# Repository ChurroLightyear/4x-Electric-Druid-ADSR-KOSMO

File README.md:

# 4x-Electric-Druid-ADSR-KOSMO (UN TESTED)
A kind of crude envelope generator based around the ENVGEN 8C chip from electric druid and LMNC's circuit for the mini ADSR

I originally designed this on stripboard which It's worked great since but after moving my modules around and debugging over 50+ wires for which one may have shorted I decided to make a PCB layout. The old stripboard layout works fine but It's ALOT of wired connections and 2 boards.
This is a PCB layout for a 4 envelope generators based around LMNC's ADSR and the electric druid chip ENV GEN 8C.
This has the a level knob added and it's 6 knobs ADSR time and level with a mode switch (ADSR, Gated loop and loop) and 16 jacks (a gate input, 2 output and a negative output for each envelope)
Theres a panel layout with the holes for everything except the LED's which I added after. I'm still using my old painted aluminum panel for this but The space for optional LEDs are on the Main PCB.
There's also holes on the panel that fit the Tayda stripboard mounting holes.
The LEDs are connected directly to the output so there may be some voltage drop but I've not noticed anything on the stripboard version
This module is untested the stripboard layout works

The files for the PCBs are all layed out in Kicad

UPDATE circuit has been verified and tested but there is a single missing trace for envelope 3
Between R27 and R49 be sure to a trace or jumper between those Reuploading the fixed board

The files on github have been updated with the missing trace, Everything should work as expected.
Added a BOM for both boards***

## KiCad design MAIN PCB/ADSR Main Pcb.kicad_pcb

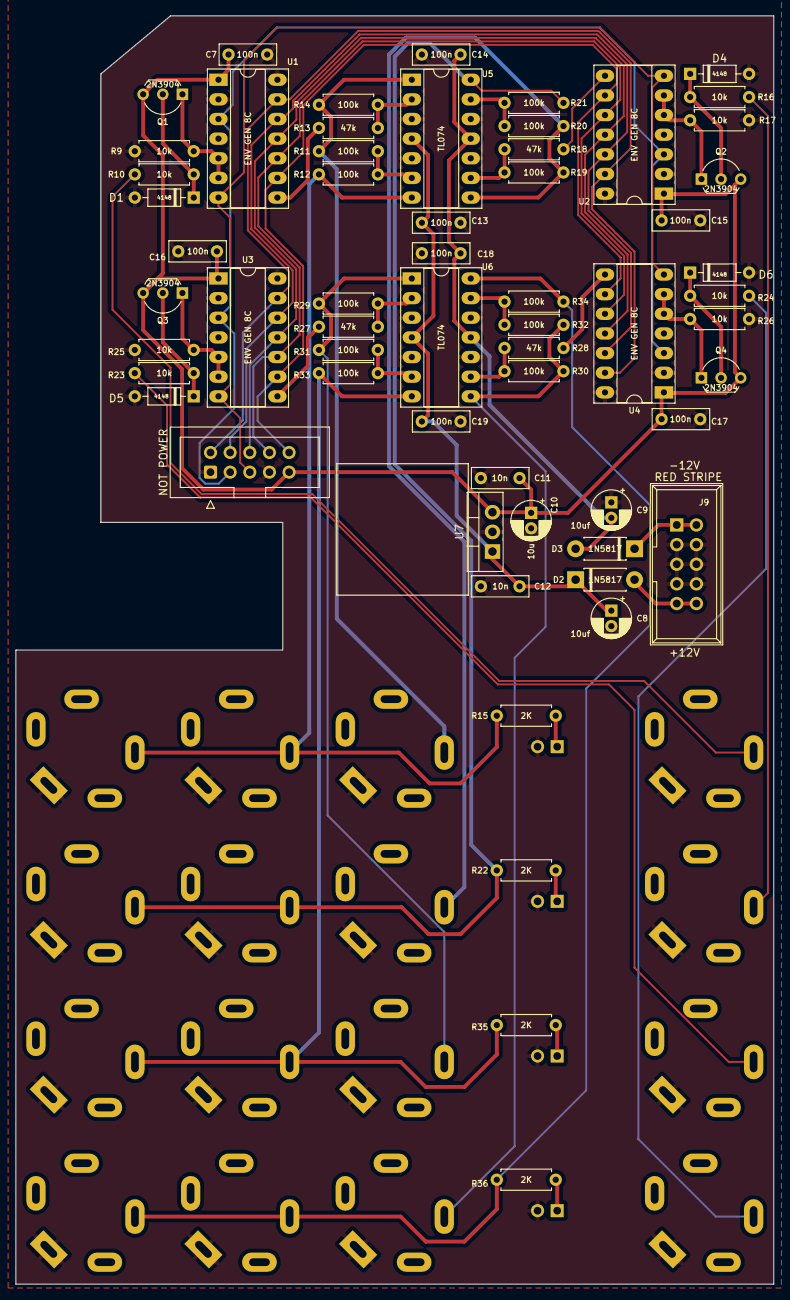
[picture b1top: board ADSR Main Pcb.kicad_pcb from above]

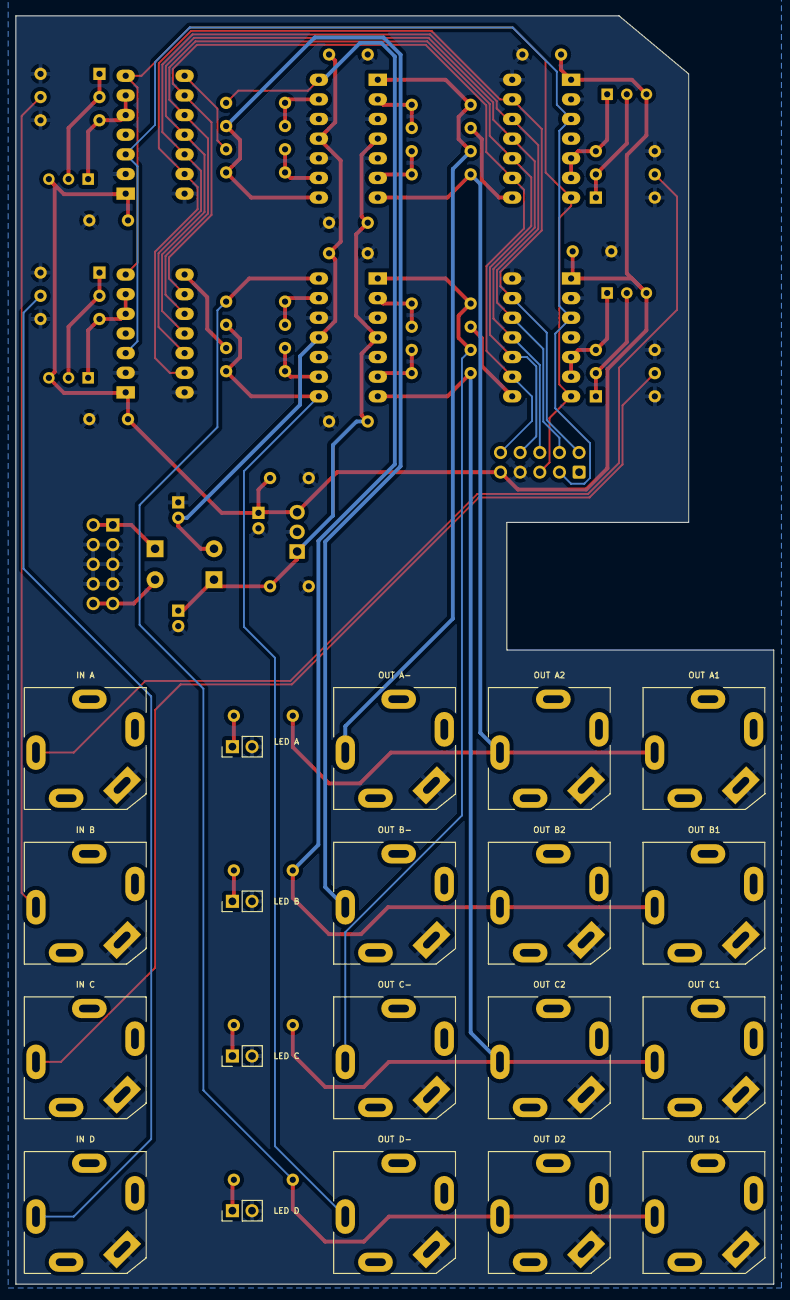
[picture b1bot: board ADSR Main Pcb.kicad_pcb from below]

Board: 2 copper layers, 98.0 x 164.0 mm, 80 parts (20 on the bottom side), 49 nets.

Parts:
C7, C13, C14, C15, C16, C17, C18, C19: 100n; C_Rect_L7.2mm_W2.5mm_P5.00mm_FKS2_FKP2_MKS2_MKP2
C8, C9: 10uf; CP_Radial_D5.0mm_P2.00mm
C10: 10u; CP_Radial_D5.0mm_P2.00mm
C11, C12: 10n; C_Rect_L7.2mm_W2.5mm_P5.00mm_FKS2_FKP2_MKS2_MKP2
D1, D4, D5, D6: 1N4148; D_DO-35_SOD27_P7.62mm_Horizontal
D2, D3: 1N5817; D_DO-41_SOD81_P7.62mm_Horizontal
IN A: Jack_6.35mm_PJ_629HAN_slots
IN B: Jack_6.35mm_PJ_629HAN_slots
IN C: Jack_6.35mm_PJ_629HAN_slots
IN D: Jack_6.35mm_PJ_629HAN_slots
J9: POWER; Power_Header
LED A: LED A; PinHeader_1x02_P2.54mm_Vertical
LED B: LED B; PinHeader_1x02_P2.54mm_Vertical
LED C: LED C; PinHeader_1x02_P2.54mm_Vertical
LED D: LED D; PinHeader_1x02_P2.54mm_Vertical
NOT POWER: IDC-Header_2x05_P2.54mm_Vertical
OUT A1, OUT A2: Jack_6.35mm_PJ_629HAN_slots
OUT A-: Jack_6.35mm_PJ_629HAN_slots
OUT B1, OUT B2: Jack_6.35mm_PJ_629HAN_slots
OUT B-: Jack_6.35mm_PJ_629HAN_slots
OUT C1, OUT C2: Jack_6.35mm_PJ_629HAN_slots
OUT C-: Jack_6.35mm_PJ_629HAN_slots
OUT D1, OUT D2: Jack_6.35mm_PJ_629HAN_slots
OUT D-: Jack_6.35mm_PJ_629HAN_slots
Q1, Q2, Q3, Q4: 2N3904; TO-92_Inline_Wide
R9, R10, R16, R17, R23, R24, R25, R26: 10k; R_Axial_DIN0207_L6.3mm_D2.5mm_P7.62mm_Horizontal
R11, R12, R14, R19, R20, R21, R29, R30, R31, R32, R33, R34: 100k; R_Axial_DIN0207_L6.3mm_D2.5mm_P7.62mm_Horizontal
R13, R18, R27, R28: 47k; R_Axial_DIN0207_L6.3mm_D2.5mm_P7.62mm_Horizontal
R15, R22, R35, R36: 2K; R_Axial_DIN0207_L6.3mm_D2.5mm_P7.62mm_Horizontal
U1, U2, U3, U4: ENV GEN 8C; DIP-14_W7.62mm_Socket_LongPads
U5, U6: TL074; DIP-14_W7.62mm_Socket_LongPads
U7: LM7809; TO-220-3_Vertical

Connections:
+5V: C7.2, C10.1, C11.1, C15.2, C16.2, C17.2, NOT POWER.9, Q1.3 (C), Q2.3 (C), Q3.3 (C), Q4.3 (C), U1.1 (5v), U2.1 (5v), U3.1 (5v), U4.1 (5v), U7.3 (VO)
+12V: C8.1, C12.2, C13.1, C19.1, D2.1 (K), U5.4 (V+), U6.4 (V+), U7.1 (VI)
-12V: C9.2, C14.2, C18.2, D3.2 (A), U5.11 (V-), U6.11 (V-)
ATK: NOT POWER.2, U1.13 (ATK), U2.13 (ATK), U3.13 (ATK), U4.13 (ATK)
DEC: NOT POWER.6, U1.11 (DEC), U2.11 (DEC), U3.11 (DEC), U4.11 (DEC)
ENV A: R13.1, U1.8 (OUT)
ENV B: R18.1, U2.8 (OUT)
ENV C: R27.1, U3.8 (OUT)
ENV D: R28.1, U4.8 (OUT)
GATE A: Q1.1 (E), R9.1, U1.5 (GATE), U1.6 (TRIG)
GATE B: Q2.1 (E), R17.1, U2.5 (GATE), U2.6 (TRIG)
GATE C: Q3.1 (E), R25.1, U3.5 (GATE), U3.6 (TRIG)
GATE D: Q4.1 (E), R26.1, U4.5 (GATE), U4.6 (TRIG)
GND: C7.1, C8.2, C9.1, C10.2, C11.2, C12.1, C13.2, C14.1, C15.1, C16.1, C17.1, C18.1, C19.2, D1.2 (A), D4.2 (A), D5.2 (A), D6.2 (A), IN A.S, IN B.S, IN C.S, IN D.S, J9.3 (GND), J9.4 (GND), J9.5 (GND), J9.6 (GND), J9.7 (GND), J9.8 (GND), LED A.2, LED B.2, LED C.2, LED D.2, NOT POWER.1, NOT POWER.7, OUT A1.S, OUT A2.S, OUT A-.S, OUT B1.S, OUT B2.S, OUT B-.S, OUT C1.S, OUT C2.S, OUT C-.S, OUT D1.S, OUT D2.S, OUT D-.S, R9.2, R17.2, R25.2, R26.2, U1.2 (Punch), U1.14 (GND), U2.2 (Punch), U2.14 (GND), U3.2 (Punch), U3.14 (GND), U4.2 (Punch), U4.14 (GND), U5.3 (+), U5.5 (+), U5.10 (+), U5.12 (+), U6.3 (+), U6.5 (+), U6.10 (+), U6.12 (+), U7.2 (GND)
LVL: NOT POWER.4, U1.12 (LVL), U2.12 (LVL), U3.12 (LVL), U4.12 (LVL)
MODE: NOT POWER.3, U1.3 (MODE), U2.3 (MODE), U3.3 (MODE), U4.3 (MODE)
unnamed: D1.1 (K), Q1.2 (B), R10.2
unnamed: D2.2 (A), J9.9 (+12V), J9.10 (+12V)
unnamed: D3.1 (K), J9.1 (-12V), J9.2 (-12V)
unnamed: D4.1 (K), Q2.2 (B), R16.2
unnamed: D5.1 (K), Q3.2 (B), R23.2
unnamed: D6.1 (K), Q4.2 (B), R24.2
unnamed: IN A.T, R10.1
unnamed: OUT A1.T, OUT A2.T, R12.2, R15.1, U5.7
unnamed: OUT A-.T, R11.1, R14.2, U5.1
unnamed: LED A.1, R15.2
unnamed: IN B.T, R16.1
unnamed: LED B.1, R22.2
unnamed: OUT B1.T, OUT B2.T, R21.2, R22.1, U5.14
unnamed: OUT B-.T, R19.2, R20.1, U5.8
unnamed: IN C.T, R23.1
unnamed: IN D.T, R24.1
unnamed: LED C.1, R35.2
unnamed: OUT C1.T, OUT C2.T, R33.2, R35.1, U6.7
unnamed: OUT C-.T, R29.2, R31.1, U6.1
unnamed: LED D.1, R36.2
unnamed: OUT D1.T, OUT D2.T, R34.2, R36.1, U6.14
unnamed: OUT D-.T, R30.2, R32.1, U6.8
unnamed: R13.2, R14.1, U5.2 (-)
unnamed: R11.2, R12.1, U5.6 (-)
unnamed: R18.2, R19.1, U5.9 (-)
unnamed: R20.2, R21.1, U5.13 (-)
unnamed: R27.2, R29.1, U6.2 (-)
unnamed: R31.2, R33.1, U6.6 (-)
unnamed: R28.2, R30.1, U6.9 (-)
unnamed: R32.2, R34.1, U6.13 (-)
REL: NOT POWER.10, U1.9 (REL), U2.9 (REL), U3.9 (REL), U4.9 (REL)
SUS: NOT POWER.8, U1.10 (SUS), U2.10 (SUS), U3.10 (SUS), U4.10 (SUS)
TIME: NOT POWER.5, U1.7 (TIME), U2.7 (TIME), U3.7 (TIME), U4.7 (TIME)
